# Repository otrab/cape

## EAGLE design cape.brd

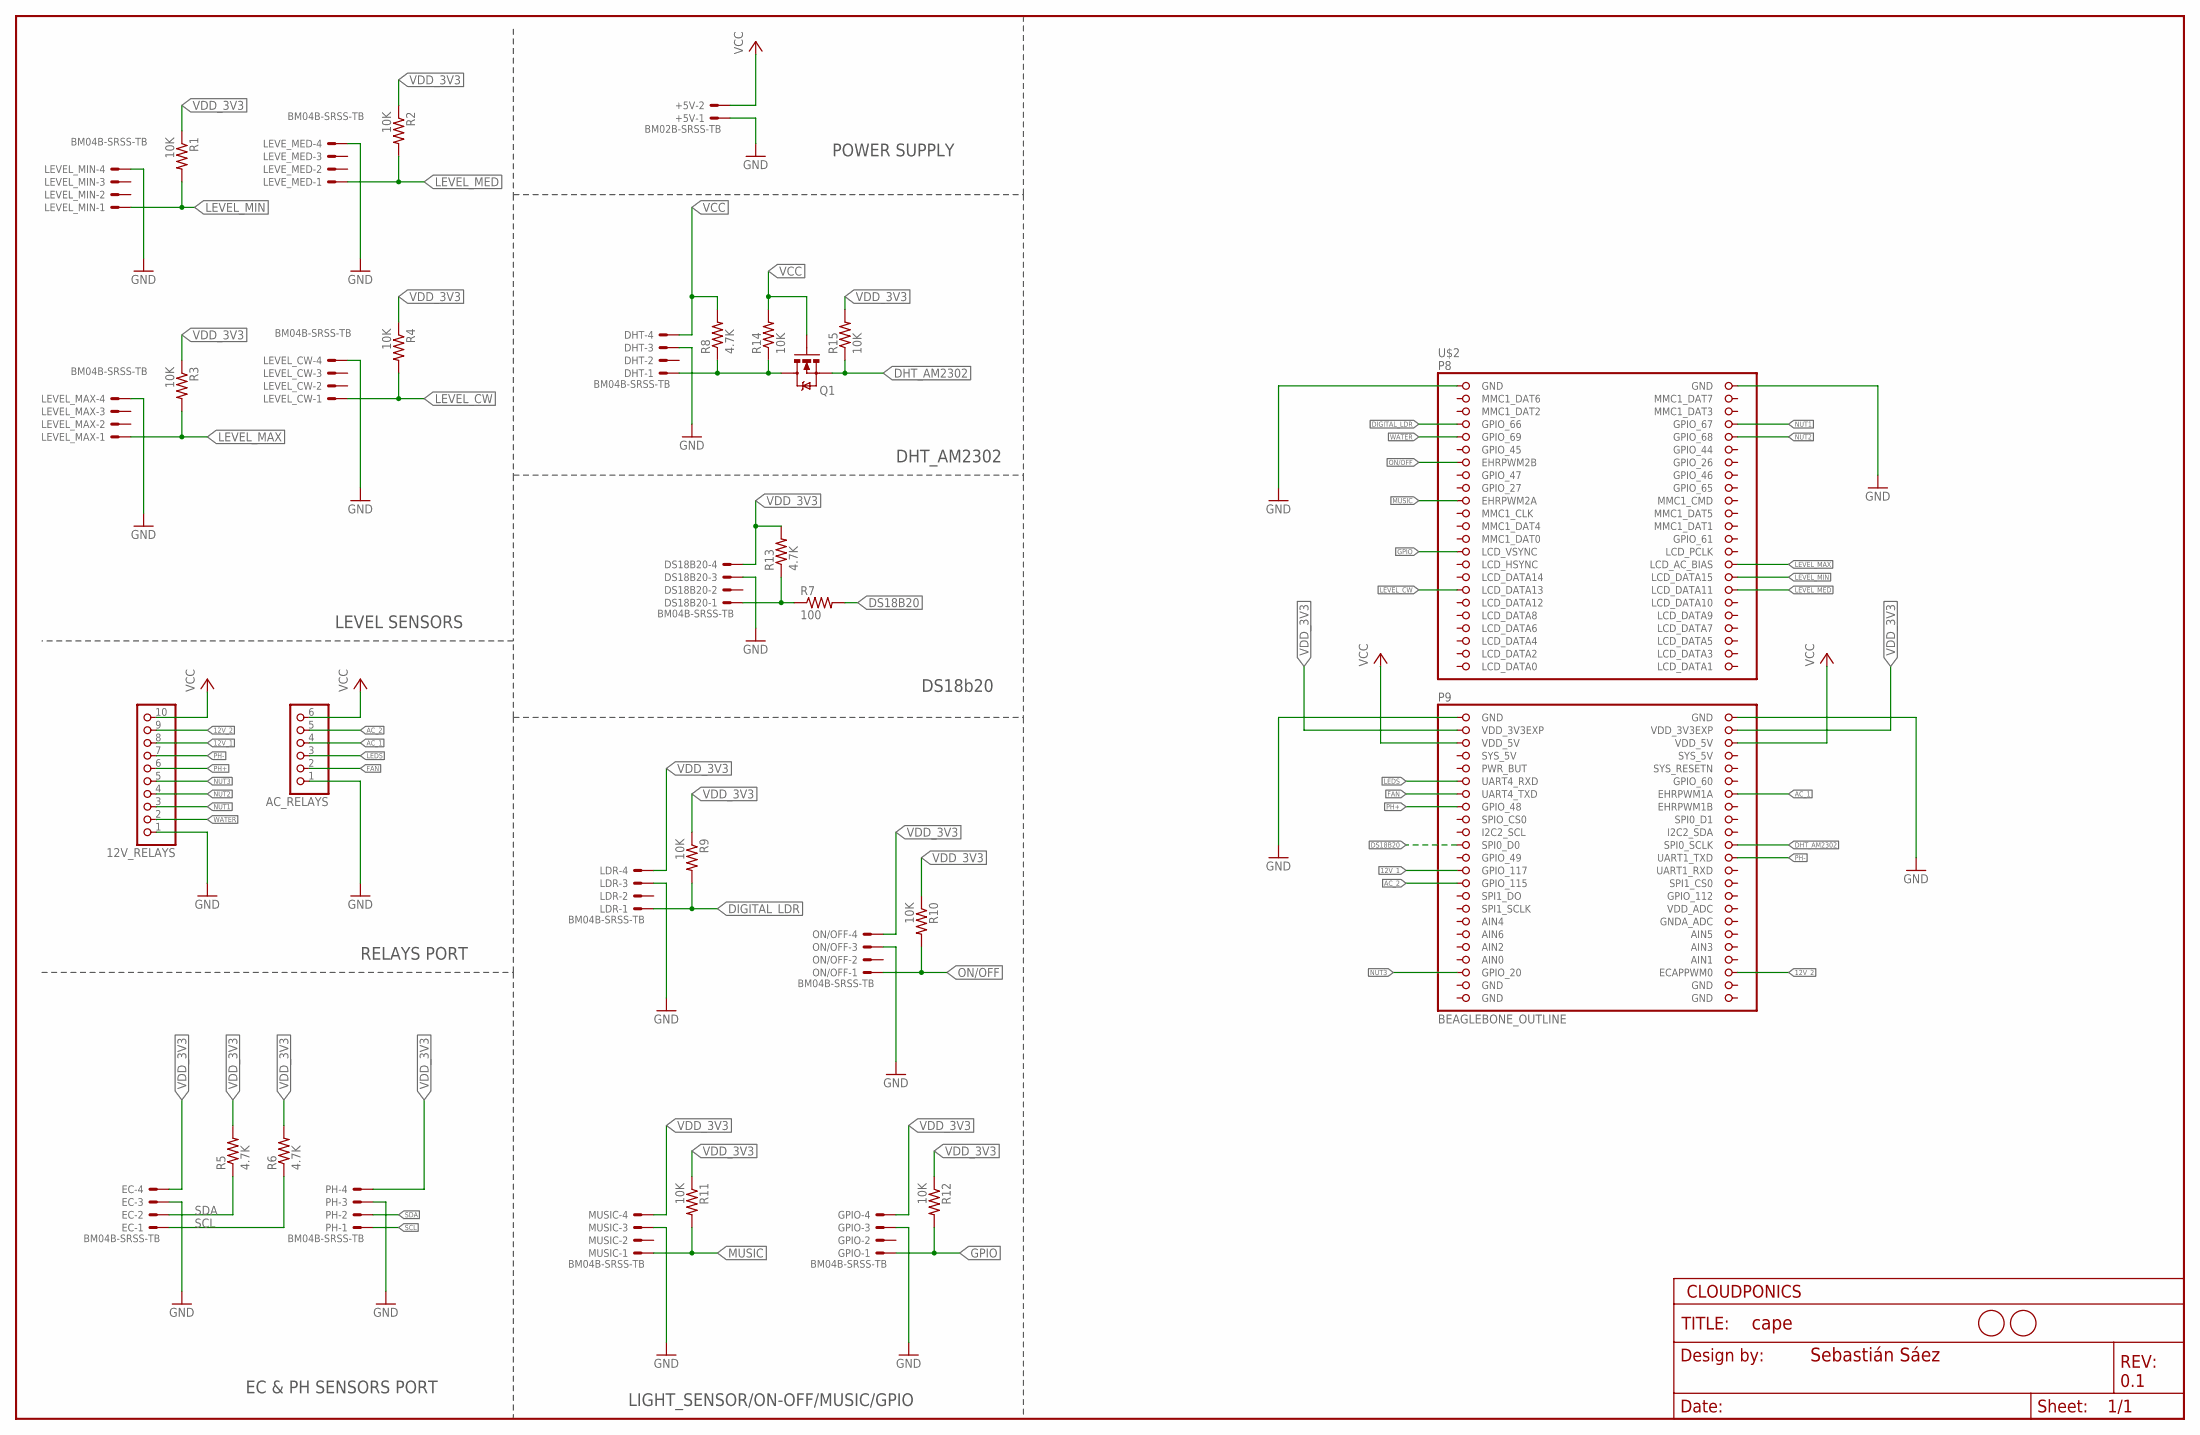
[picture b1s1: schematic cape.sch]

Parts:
12V_RELAYS: PINHD-1X10; 1X10-BIG
+5V: BM02B-SRSS-TB
AC_RELAYS: PINHD-1X6B; 1X06-BIG
DHT: BM04B-SRSS-TB
DS18B20: BM04B-SRSS-TB
EC: BM04B-SRSS-TB
FRAME1: FRAME-LEDGER; CREATIVE_COMMONS
GPIO: BM04B-SRSS-TB
LDR: BM04B-SRSS-TB
LEVEL_CW: BM04B-SRSS-TB
LEVEL_MAX: BM04B-SRSS-TB
LEVEL_MIN: BM04B-SRSS-TB
LEVE_MED: BM04B-SRSS-TB
MUSIC: BM04B-SRSS-TB
ON/OFF: BM04B-SRSS-TB
PH: BM04B-SRSS-TB
Q1: MOSFET-NCHANNELBSS123LT1G; SOT23-3
R1, R2, R3, R4, R9, R10, R11, R12, R14, R15: 10K; R0805
R5, R6, R8, R13: 4.7K; R0805
R7: 100; R0805
U$1, U$3: FIDUCIAL; FIDUCIAL_1MM
U$2: BEAGLEBONE_OUTLINE; BEAGLEBONE_SHIELD

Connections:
12V_1: 12V_RELAYS.8, U$2.71 (GPIO_117)
12V_2: 12V_RELAYS.9, U$2.88 (ECAPPWM0)
AC_1: AC_RELAYS.4, U$2.60 (EHRPWM1A)
AC_2: AC_RELAYS.5, U$2.73 (GPIO_115)
AIN0: U$2.85 (AIN0)
DHT_AM2302: Q1.2 (S), R15.1, U$2.68 (SPI0_SCLK)
DIGITAL_LDR: LDR.1, R9.2, U$2.7 (GPIO_66)
DS18B20: R7.2, U$2.67 (SPI0_D0)
FAN: AC_RELAYS.2, U$2.59 (UART4_TXD)
GND: 12V_RELAYS.1, +5V.1, AC_RELAYS.1, DHT.3, DS18B20.3, EC.3, GPIO.3, LDR.3, LEVEL_MAX.4, LEVEL_MIN.4, LEVE_MED.4, MUSIC.3, ON/OFF.3, PH.3, U$2.1 (GND), U$2.2 (GND), U$2.47 (GND), U$2.48 (GND), U$2.89 (GND), U$2.90 (GND), U$2.91 (GND), U$2.92 (GND)
GPIO: GPIO.1, R12.2, U$2.27 (LCD_VSYNC)
LEDS: AC_RELAYS.3, U$2.57 (UART4_RXD)
LEVEL_CW: LEVEL_CW.1, R4.2, U$2.33 (LCD_DATA13)
LEVEL_MAX: LEVEL_MAX.1, R3.2, U$2.30 (LCD_AC_BIAS)
LEVEL_MED: LEVE_MED.1, R2.2, U$2.34 (LCD_DATA11)
LEVEL_MIN: LEVEL_MIN.1, R1.2, U$2.32 (LCD_DATA15)
LEVE_CW: LEVEL_CW.4
MUSIC: MUSIC.1, R11.2, U$2.19 (EHRPWM2A)
N1: DS18B20.1, R7.1, R13.1
unnamed: DHT.1, Q1.3 (D), R8.1, R14.1
NUT1: 12V_RELAYS.3, U$2.8 (GPIO_67)
NUT2: 12V_RELAYS.4, U$2.10 (GPIO_68)
NUT3: 12V_RELAYS.5, U$2.87 (GPIO_20)
ON/OFF: ON/OFF.1, R10.2, U$2.13 (EHRPWM2B)
PH+: 12V_RELAYS.6, U$2.61 (GPIO_48)
PH-: 12V_RELAYS.7, U$2.70 (UART1_TXD)
SCL: EC.1, PH.1, R6.1
SDA: EC.2, PH.2, R5.1
SYS_5V: U$2.53 (SYS_5V)
VCC: 12V_RELAYS.10, +5V.2, AC_RELAYS.6, DHT.4, Q1.1 (G), R8.2, R14.2, U$2.51 (VDD_5V), U$2.52 (VDD_5V)
VDD_3V3: DS18B20.4, EC.4, GPIO.4, LDR.4, MUSIC.4, ON/OFF.4, PH.4, R1.1, R2.1, R3.1, R4.1, R5.2, R6.2, R9.1, R10.1, R11.1, R12.1, R13.2, R15.2, U$2.49 (VDD_3V3EXP), U$2.50 (VDD_3V3EXP)
WATER: 12V_RELAYS.2, U$2.9 (GPIO_69)

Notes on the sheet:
LEVEL SENSORS
RELAYS PORT
EC & PH SENSORS PORT
POWER SUPPLY
LIGHT_SENSOR/ON-OFF/MUSIC/GPIO
DS18b20
DHT_AM2302

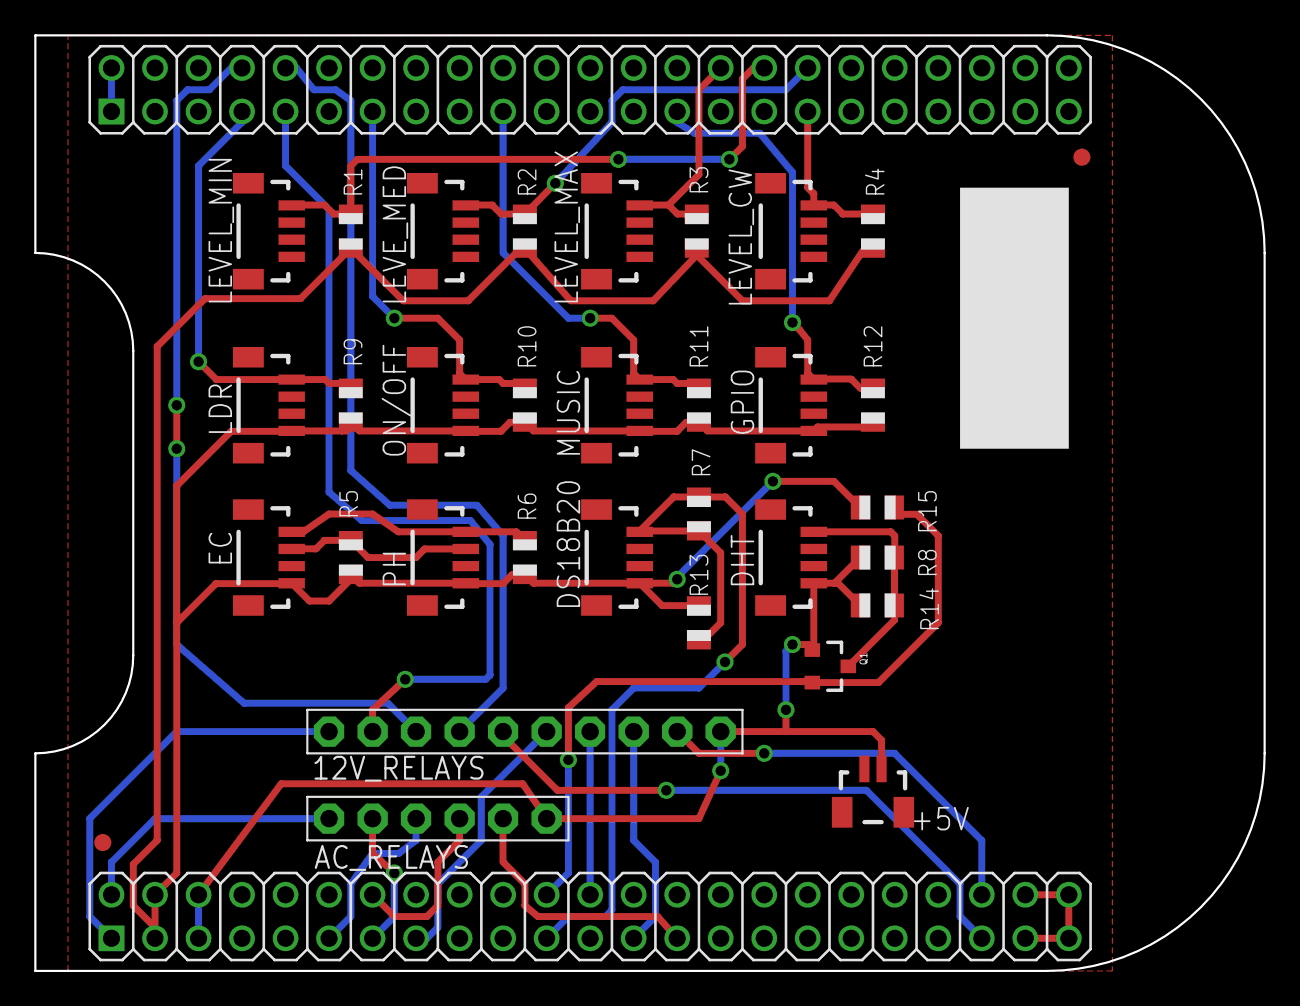
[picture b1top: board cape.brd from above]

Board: 2 copper layers, 71.8 x 54.6 mm, 35 parts (0 on the bottom side), 29 nets.

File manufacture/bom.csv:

Qty;Value;Device;Package;Parts;Description;Unit price;Total price;link
1;PINHD-1X8;PINHD-1X6B;1X06-BIG;AC_RELAYS;"Pin header 1x8 0.1 spacing""";$ 0,26;$ 0,26;http://www.digikey.com/product-detail/en/amphenol-fci/68000-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
1;100;R-US_R0805;R0805;R7;RESISTOR, American symbol;$ 0,02;$ 0,02;http://www.digikey.com/product-detail/en/yageo/RC0805FR-0710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
10;10K;R-US_R0805;R0805;R1, R2, R3, R4, R9, R10, R11, R12, R14, R15;RESISTOR, American symbol;$ 0,02;$ 0,17;http://www.digikey.com/product-detail/en/stackpole-electroni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
4;4.7K;R-US_R0805;R0805;R5, R6, R8, R13;RESISTOR, American symbol;$ 0,02;$ 0,08;http://www.digikey.com/product-detail/en/yageo/RC0805FR-074K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
1;BM02B-SRSS-TB;BM02B-SRSS-TB;BM02B-SRSS-TB;+5V;Disconnectable Crimp style connector, 1.0mm pitch2 contacts;$ 0,43;$ 0,43;http://www.digikey.com/product-detail/en/jst-sales-america-i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
12;BM04B-SRSS-TB;BM04B-SRSS-TB;BM04B-SRSS-TB;DHT, DS18B20, EC, GPIO, LDR, LEVEL_CW, LEVEL_MAX, LEVEL_MIN, LEVE_MED, MUSIC, ON/OFF, PH;Disconnectable Crimp style connector, 1.0mm pitch4 contacts;$ 0,59;$ 7,10;http://www.digikey.com/product-detail/en/jst-sales-america-i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
1;MOSFET-NCHANNELBSS123LT1G ;BSS138;SOT23-3;Q1;BSS138;$ 0,18;$ 0,18;http://www.digikey.com/product-detail/en/fairchild-semicondu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
1;PINHD-1X10;PINHD-1X10;1X10-BIG;12V_RELAYS;"Pin header 1x10 0.1 spacing""";0,413;$ 0,41;http://www.digikey.com/product-detail/en/harwin-inc/M20-9991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
2;PINHD-2X23;;;;"46 Positions Header, 0.100"" (2.54mm) Through Hole Gold";$ 0,92;$ 1,83;http://www.digikey.com/product-detail/en/sullins-connector-s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
;;;;;;;$ 10,49;

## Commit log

2016-11-17 :tada: Added .gitattributes & .gitignore files
2016-11-17 v0.1
    all the connectors in the schematics
2016-11-17 fix BB names int pinout
    in the library adafruit
2016-11-21 change conectors to smd
    and add 4 relays

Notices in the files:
parts and their libraries:
SparkFun-DiscreteSemi: Licensing: Creative Commons ShareAlike 4.0 International - https://creativecommons.org/licenses/by-sa/4.0
SparkFun-Aesthetics: Released under the Creative Commons Attribution Share-Alike 4.0 License
SparkFun-Aesthetics: https://creativecommons.org/licenses/by-sa/4.0
